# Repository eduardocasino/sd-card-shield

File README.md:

# SD Card Shield for 8-bit computers

## About

This is a functionally equivalent recreation of the latest version of Corsham's [SD Card Shield](https://www.corshamtech.com/new-version-of-sd-card-shield/). Sadly, Bob Applegate, the man and soul behind Corsham Technologies, passed away in 2023 and [his shop is no longer in business](https://www.corshamtech.com/bad-news-and-the-future/).

Bob put a lot of his work under open source licenses or in the public domain, and also shared the schematics of his boards in the spirit of the emerging personal computer industry of the late 1970s. However, this information was not always complete or up to date, and never published the files to physically reproduce his PCBs (logically, as this was also a business to him) and now those boards are not available anymore.

I have been able to reverse engineer the design from the schematic of previous versions, which is available, and from photos of revisions 6 and 9.

~~WARNING: This design has not been tested yet. Use at your own risk!~~

The board has been tested working with a KIM-1 and Corsham's xKIM monitor but, still, use at your own risk!

## Licensing

This is a personal project that I am sharing in case it is of interest to any retrocomputing enthusiast and all the information in this repository is provided "as is", without warranty of any kind. I am not liable for any damages that may occur, whether it be to individuals, objects, KIM-1 computers, kittens or any other pets. **It should also be noted that everything in this repository is a work in progress, has not been tested and may contain errors, therefore anyone who chooses to use it does so at their own risk**.

This work is licensed under a [Creative Commons Attribution-ShareAlike 4.0 International License](http://creativecommons.org/licenses/by-sa/4.0/).

See the LICENSE.md file for details.

## Acknowledgements

* Bob Applegate, for the original design. 
* Hans Otten and his [Retro Computing blog](http://retro.hansotten.nl/). Pictures and running some checks on his rev6 board.

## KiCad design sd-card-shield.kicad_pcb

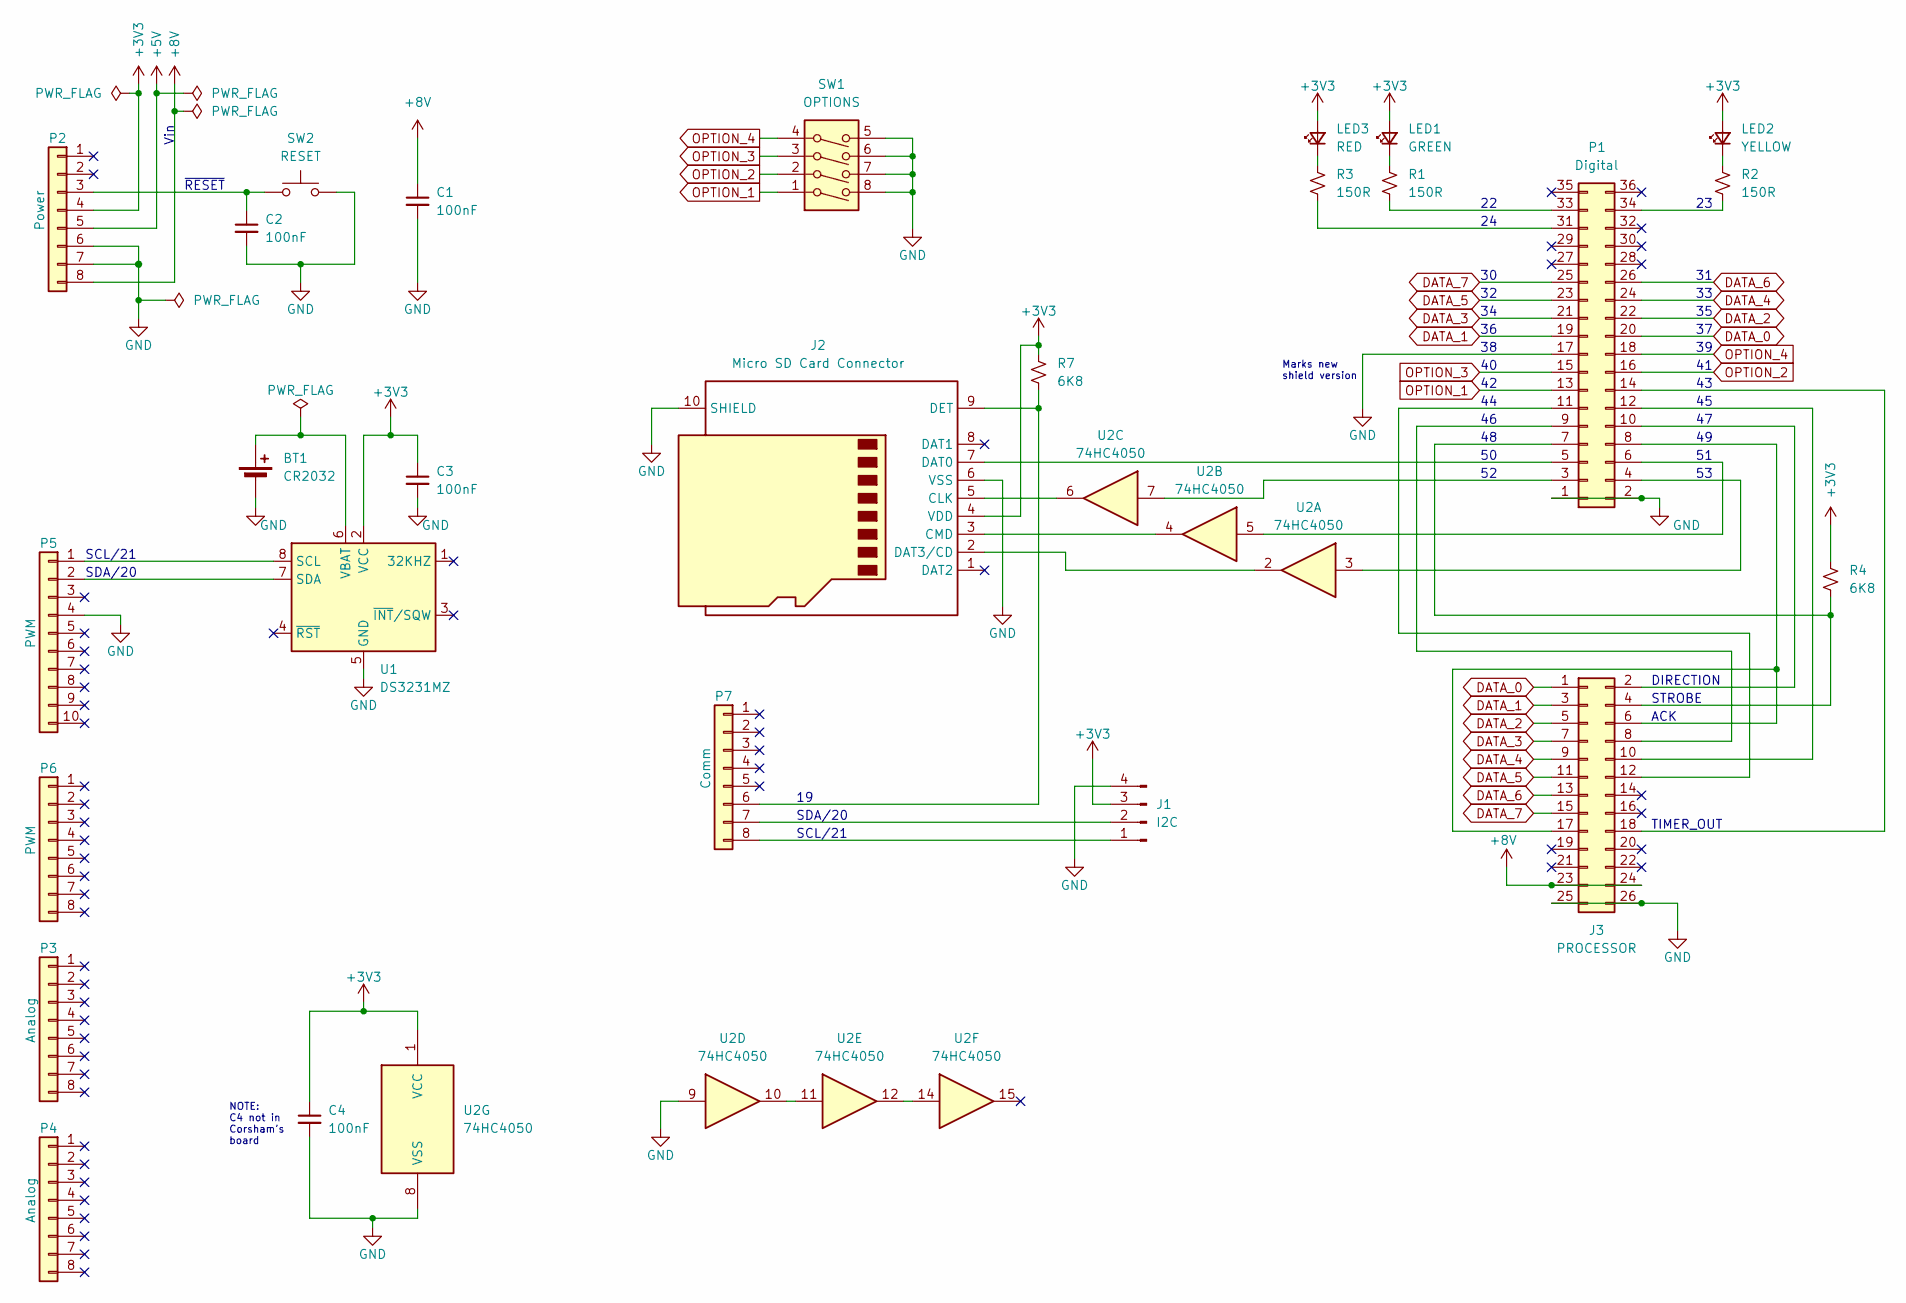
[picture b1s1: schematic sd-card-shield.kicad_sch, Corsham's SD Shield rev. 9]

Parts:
BT1: CR2032; BAT_CR2032-BS-06-B; LCSC C964760
C1, C2, C3, C4: 100nF; C_0603_1608Metric; LCSC C2762593
J1: I2C; PinHeader_1x04_P2.54mm_Vertical
J2: Micro SD Card Connector; SD_Card_Holder_SMD_WQ21801-B2180-7F
J3: PROCESSOR; IDC-Header_2x13_P2.54mm_Vertical; LCSC C7501247
LED1: GREEN; LED_0603_1608Metric; PART SML-D12P8WT86; LCSC C510026
LED2: YELLOW; LED_0603_1608Metric; PART SML-D12Y8WT86; LCSC C2840179
LED3: RED; LED_0603_1608Metric; PART SML-D12V8WT86; LCSC C2693607
P1: Digital; PinSocket_2x18_P2.54mm_Vertical
P2: Power; PinSocket_1x08_P2.54mm_Vertical
P3, P4: Analog; PinSocket_1x08_P2.54mm_Vertical
P5: PWM; PinSocket_1x10_P2.54mm_Vertical
P6: PWM; PinSocket_1x08_P2.54mm_Vertical
P7: Comm; PinSocket_1x08_P2.54mm_Vertical
R1, R2, R3: 150R; R_0603_1608Metric; LCSC C270843
R4, R7: 6K8; R_0603_1608Metric; LCSC C2074375
SW1: OPTIONS; SW_DIP_SPSTx04_Slide_6x10.22_P2.54mm_DSIC04LSGET; LCSC C54950
SW2: RESET; SW_SPST_TL3305A; LCSC C2886899
U1: DS3231MZ; SOIC-8_3.9x4.9mm_P1.27mm; LCSC C107410
U2: 74HC4050; SOP-16_3.9x9.9mm_P1.27mm; LCSC C43181

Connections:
+3V3: C3.1, C4.1, J1.3, J2.4 (VDD), LED1.2 (A), LED2.2 (A), LED3.2 (A), P2.4, R4.1, R7.1, U1.2 (VCC), U2.1 (VCC)
+5V: P2.5
+8V: C1.1, J3.23, J3.24, P2.8
DATA_0: J3.1, P1.20
DATA_1: J3.3, P1.19
DATA_2: J3.5, P1.22
DATA_3: J3.7, P1.21
DATA_4: J3.9, P1.24
DATA_5: J3.11, P1.23
DATA_6: J3.13, P1.26
DATA_7: J3.15, P1.25
GND: BT1.2 (-), C1.2, C2.2, C3.2, C4.2, J1.4, J2.6 (VSS), J2.10 (SHIELD), J3.25, J3.26, P1.1, P1.2, P1.17, P2.6, P2.7, P5.4, SW1.5, SW1.6, SW1.7, SW1.8, SW2.1, U1.5 (GND), U2.8 (VSS), U2.9
unnamed: BT1.1 (+), U1.6 (VBAT)
unnamed: J1.1, P7.8
unnamed: J1.2, P7.7
unnamed: J2.5 (CLK), U2.6
unnamed: J2.3 (CMD), U2.4
unnamed: J2.7 (DAT0), P1.5
unnamed: J2.2 (DAT3/CD), U2.2
unnamed: J2.9 (DET), P7.6, R7.2
unnamed: J3.2, P1.10
unnamed: J3.4, P1.7, R4.2
unnamed: J3.8, P1.9
unnamed: J3.10, P1.12
unnamed: J3.12, P1.11
unnamed: J3.6, J3.17, P1.8
unnamed: J3.18, P1.14
unnamed: LED1.1 (K), R1.1
unnamed: LED2.1 (K), R2.1
unnamed: LED3.1 (K), R3.1
unnamed: P1.3, U2.7
unnamed: P1.4, U2.3
unnamed: P1.6, U2.5
unnamed: P1.31, R3.2
unnamed: P1.33, R1.2
unnamed: P1.34, R2.2
unnamed: C2.1, P2.3, SW2.2
unnamed: P5.1, U1.8 (SCL)
unnamed: P5.2, U1.7 (SDA)
unnamed: U2.10, U2.11
unnamed: U2.12, U2.14
OPTION_1: P1.13, SW1.1
OPTION_2: P1.16, SW1.2
OPTION_3: P1.15, SW1.3
OPTION_4: P1.18, SW1.4

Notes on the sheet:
TIMER_OUT
Vin
~{RESET}
NOTE: C4 not in Corsham's board
SDA/20
STROBE
DIRECTION
SCL/21
Marks new shield version
ACK

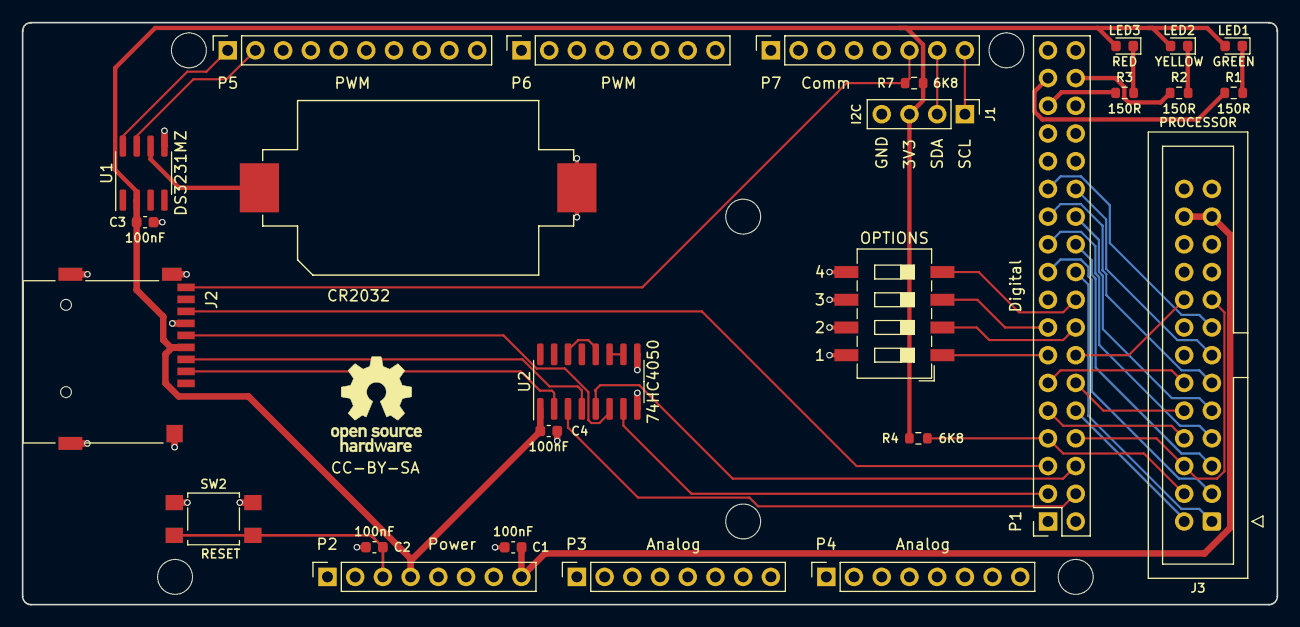
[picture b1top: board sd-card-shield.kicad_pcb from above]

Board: 2 copper layers, 115.0 x 53.3 mm, 33 parts (0 on the bottom side), 44 nets.

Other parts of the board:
MH1, MH2, MH3, MH4, MH5, MH6: MountingHole_3.2mm

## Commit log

2023-11-24 Fix images
2024-08-16 Update README with board working status
2024-08-16 Minor README update

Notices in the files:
README.md:
Licensing:
[CC BY-SA 4.0](http:
CC BY-SA 4.0
sd-card-shield.kicad_pcb:
CC-BY-SA
